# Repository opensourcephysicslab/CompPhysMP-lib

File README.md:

# Computational Physics MicroPython libraries

## Introduction
This repo contains MicroPython code developed to support computational physics in a laboratory setting, mainly reading data from sensors and displaying results.

## Concept of unified and simplified drivers/modules

In order to make computational physics laboratory activities an enjoyable experience for students and instructors, the developer(s) have made simplified drivers that focus on the key features of sensors with a unified interface among sensors of the same type.

For instance, LIS3HD and ADX345 are 3-axis accelerometers made by different companies with different accuracy and features that make them not exactly interchangeable. But by the magic of unification, regardless which accelerometer you choose to use, a call to accelerometer.read_mss() will always return a tuple of accelerations (actually, force over a fixed mass) in m/s/s unit such as (0.15,-0.23,9.72).

In pursuing for this unified interface for a beginner's sake, the differences among sensors of the same type are NOT addressed, such as some accelerometers have up to 400Hz data rate and others have extended range such as +-16g, yet some can detect knock, double click, issue interrupts under certain conditions (such as free falling). This is definitely an oversimplification of what each sensor can do.

The outcome is hopefully a quick way to utilizing the sensors with minimal efforts.

Also, those who are curious about how these sensors work will find the oversimplified drivers/modules code much easier to understand compared with a more "full feature" driver. In each case, the user is strongly encouraged to consult the sensor's specification sheet. 

To address the omission of some sensor features, other github repos that have "full feature" drivers/modules are included as submodules. These have been tested to work on at least one MicroPython platform, i.e. RP2040, if not more.

## A warning:

Compared with the more unified writing styles of the drivers/modules, the included submodules were all written by different developers, each having their own styles and conventions. It is like watching YouTube videos of physics lectures from different professors. Each one has their own symbols and styles so it could be disorienting for beginners. Reading the unified drivers/modules code before a "full feature" module is highly recommended. For support on any submodules, please contact the developers of those submodules.

## Conventions:

Any files or folders named Driver_[git_handle]_[sensor_model] is a unified and simplified driver/module. Example: Driver_LiuDr_LIS3DH.py

Any unified and simplified driver/module MUST define an embedded example with 
`if __name__=='_main__'` conditional and assume the sensor is connected to an Adafruit KB2040 via the STEMMA-QT connector, with no other dependency. So if executed directly will provide a basic printout in console such as printing ax,ay,az for an accelerometer or temperature and pressure for a barometer.

## Installation:

The Adafruit KB2040 is recommended. It is small, inexpensive, and has a large file storage, albeit not a RAM size. It also has a STEMMA-QT connector that can help students and instructors quickly set up an experiment without breadboard experiece [KB2040](https://www.adafruit.com/product/5302)

You need to solder headers to your KB2040. The [primary guide](https://learn.adafruit.com/adafruit-kb2040/overview) has tutorial on how to.

The Thonny IDE is highly recommended for editing your code and interacting with your board and sensors. [Thonny](https://thonny.org/)

You can install MicroPython firmware to some of the dev board via Thonny. For KB2040, download the firmware for Adafruit Feather RP2040 (same firmware as KB2040) [here](https://micropython.org/download/ADAFRUIT_FEATHER_RP2040/). Hold the boot button, plug in to USB, wait for a moment and release the boot button. The board enumerates a flash drive. Drag+drop the firmware into the flash drive. The firmware will cause the flash drive to disappear. After about 30 seconds, you can press reset and go to Thonny to connect to it.

Cloning this repo is highly recommended but for simplicity you can just download the repo in a .zip file. Copy lib folder to the root folder of your MicroPython board. Be mindful how many external submodules you are copying. The recommendation is to not copy anything in lib that doesn't start with Driver_[git_handle].py unless the example code requires certain files.

Example code is in the top-level folder and can be copied to the root folder of your MicroPython board. Example: copy LIS3DH_SH1117_display.py to your board. Open the example and read the comments at the top to see what hardware you need and what library you need to copy to what destination.

All example code are written for Adafruit KB2040 board. If you are using a different board, open the code and make necessary changes to the 'i2c=I2C(...)' line to match your board. Then run this code in Thonny.

## Submodules not included

Some git projects that include full-feature drivers/modules are not included as submodules in this repo because of various reasons. One of them would be the repo contains more than just a MicroPython sensor driver/module but also other things not related to our efforts, such as custom firmware images for specific boards, circuit board designs etc. When such inclusion becomes too confusing to include, the repo's link will be included below with some explanation on where the driver/module is.

[tinypico](https://github.com/tinypico/tinypico-micropython) includes an LIS3DH MicroPython driver that is tested to work, with extended features.

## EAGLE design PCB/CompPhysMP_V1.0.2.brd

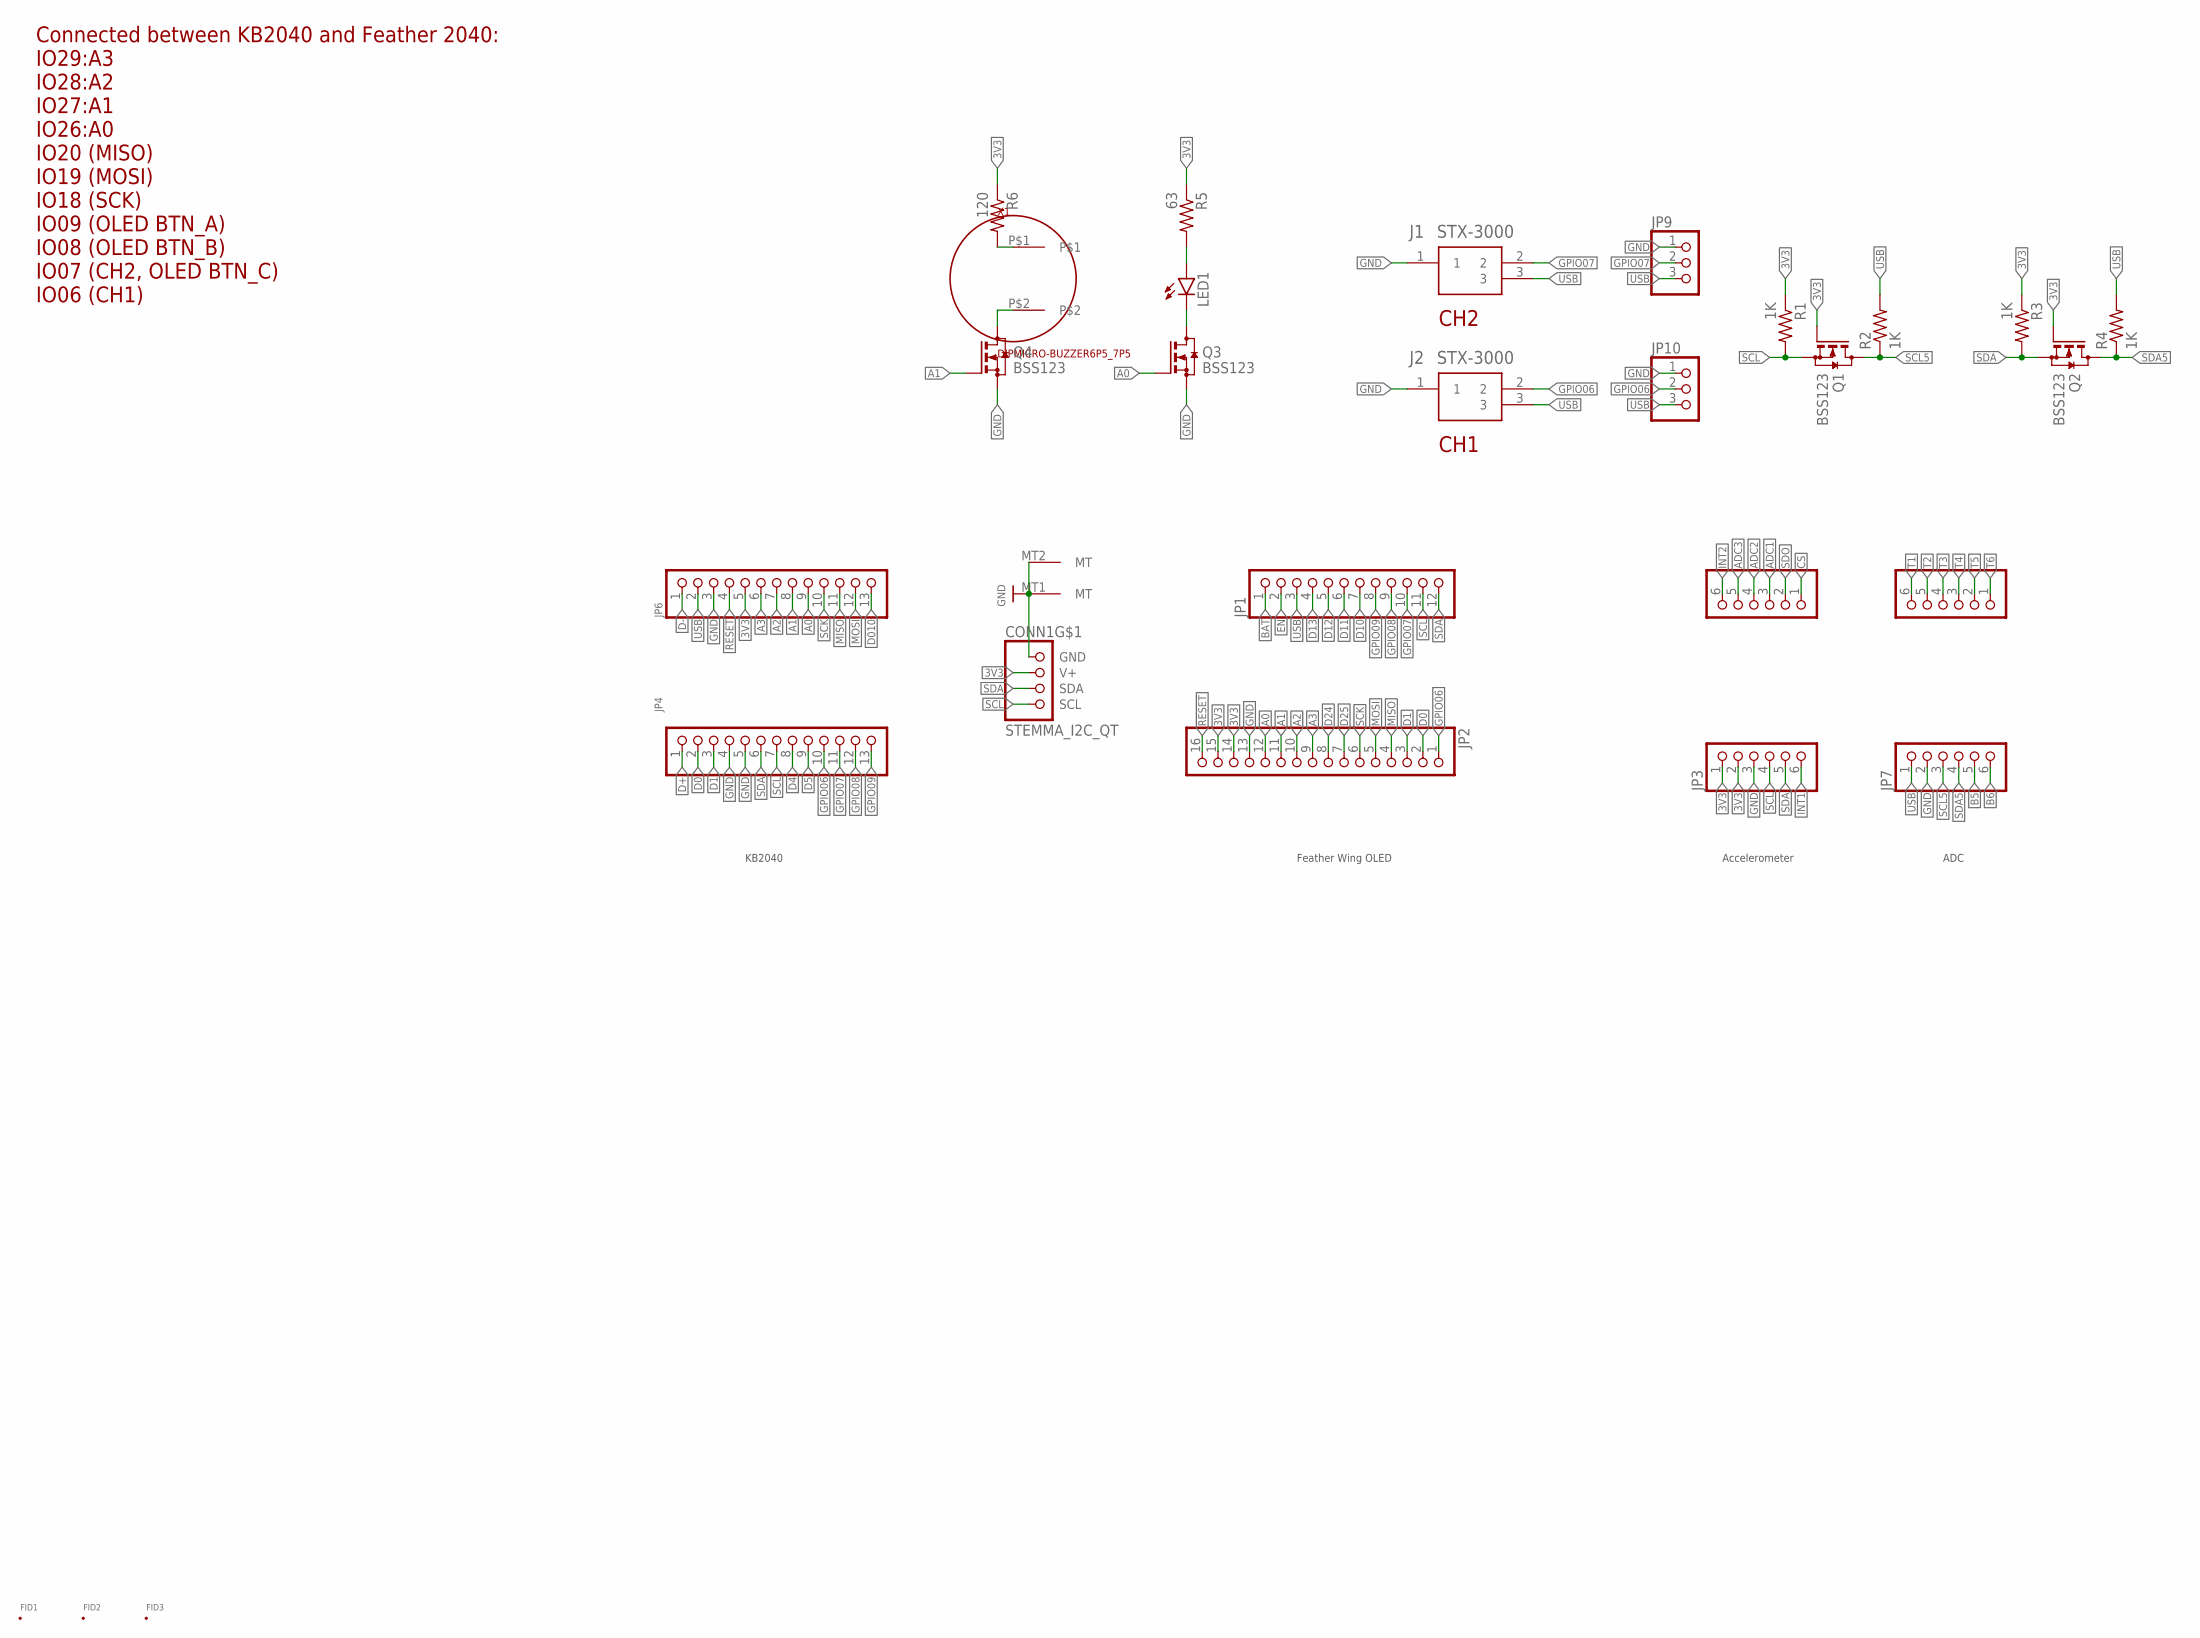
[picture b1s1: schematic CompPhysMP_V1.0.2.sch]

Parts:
CONN1: STEMMA_I2C_QT; JST_SH4
FID1, FID2, FID3: FID_50MIL; FID_050
J1, J2: STX-3000; STX3000
JP1: PINHD-1X12; 1X12
JP2: PINHD-1X16; 1X16
JP3, JP5, JP7, JP8: HEADER-1X670MIL; 1X06_ROUND_70
JP4, JP6: PINHD-1X13; 1X13
JP9, JP10: PINHD-1X3SMALL-PADS; 1X03-BIG
LED1: LED5MM
Q1, Q2, Q3, Q4: BSS123; SOT23
R1, R2, R3, R4: 1K; R0805
R5: 63; R0805
R6: 120; R0805
X1: DIPMICRO-BUZZER6P5_7P5; BUZZER-6P5-7P5

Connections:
3V3: CONN1.2 (V+), JP2.14, JP2.15, JP3.1, JP3.2, JP6.5, Q1.1 (G), Q2.1 (G), R1.1, R3.1, R5.1, R6.1
!RESET: JP2.16, JP6.4
A0: JP2.12, JP6.9, Q3.1 (G)
A1: JP2.11, JP6.8, Q4.1 (G)
A2: JP2.10, JP6.7
A3: JP2.9, JP6.6
ADC1: JP5.3
ADC2: JP5.4
ADC3: JP5.5
B5: JP7.5
B6: JP7.6
BAT: JP1.1
CS: JP5.1
D0: JP2.2, JP4.2
D1: JP2.3, JP4.3
D4: JP4.8
D5: JP4.9
D10: JP1.7
D010: JP6.13
D11: JP1.6
D12: JP1.5
D13: JP1.4
D24: JP2.8
D25: JP2.7
D+: JP4.1
D-: JP6.1
EN: JP1.2
GND: CONN1.1 (GND), CONN1.MT1 (MT), CONN1.MT2 (MT), J1.1, J2.1, JP2.13, JP3.3, JP4.4, JP4.5, JP6.3, JP7.2, JP9.1, JP10.1, Q3.2 (S), Q4.2 (S)
GPIO06: J2.2, JP2.1, JP4.10, JP10.2
GPIO07: J1.2, JP1.10, JP4.11, JP9.2
GPIO08: JP1.9, JP4.12
GPIO09: JP1.8, JP4.13
INT1: JP3.6
INT2: JP5.6
MISO: JP2.4, JP6.11
MOSI: JP2.5, JP6.12
unnamed: LED1.A, R5.2
unnamed: R6.2, X1.P$1
unnamed: LED1.K (C), Q3.3 (D)
unnamed: Q4.3 (D), X1.P$2
SCK: JP2.6, JP6.10
SCL: CONN1.4 (SCL), JP1.11, JP3.4, JP4.7, Q1.2 (S), R1.2
SCL5: JP7.3, Q1.3 (D), R2.1
SDA: CONN1.3 (SDA), JP1.12, JP3.5, JP4.6, Q2.2 (S), R3.2
SDA5: JP7.4, Q2.3 (D), R4.1
SDO: JP5.2
T1: JP8.6
T2: JP8.5
T3: JP8.4
T4: JP8.3
T5: JP8.2
T6: JP8.1
USB: J1.3, J2.3, JP1.3, JP6.2, JP7.1, JP9.3, JP10.3, R2.2, R4.2

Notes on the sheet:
Accelerometer
ADC
Feather Wing OLED
KB2040
Connected between KB2040 and Feather 2040: IO29:A3 IO28:A2 IO27:A1 IO26:A0 IO20 (MISO) IO19 (MOSI) IO18 (SCK) IO09 (OLED BTN_A) IO08 (OLED BTN_B) IO07 (CH2, OLED BTN_C) IO06 (CH1)
CH1
CH2

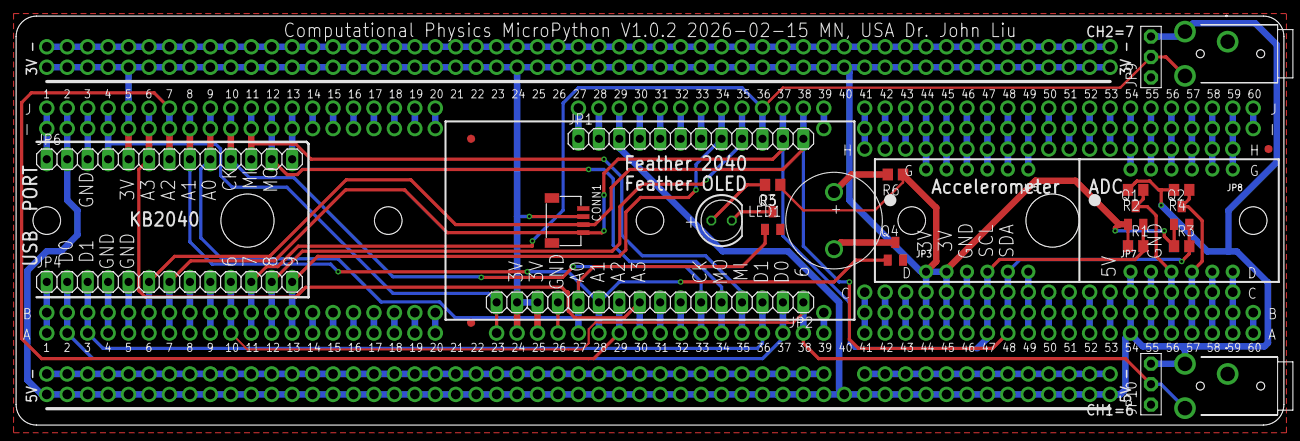
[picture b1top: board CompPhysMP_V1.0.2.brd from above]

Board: 2 copper layers, 157.5 x 50.8 mm, 28 parts (0 on the bottom side), 25 nets.

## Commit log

2024-10-18 Initial commit
    Adding 3 LiuDr drivers and several micropython libraries as submodules.
2024-10-18 Create LIS3DH_SH11107_display.py
    Example to show acceleration components and x-tilt angle on console and display x-tilt angle on OLED.
2024-10-18 Moved example code to top-level folder
2024-10-18 Update README.md
    Added detailed instructions on how to install MicroPython, where to download firmware and Thonny.
2024-10-25 Update LIS3DH_SH11107_display.py
    Made the free fall detection display persist for 2 seconds for people to see.
2024-10-26 Added spec sheets
2024-10-27 Update LIS3DH_SH11107_display.py
    Using atan2 now and cleaned up print() statement
2024-11-02 Added dev board pinout diagrams and an rp2040 analog print program
2024-11-05 Update README.md
    Minor edits
2024-11-13 Updated ADXL345 and LIS3DH modules to accept useDefaultAddr=True/False for default or alternate address
2025-02-10 Added a two-rectangle rotation demo with LIS3DH and SH1107 and updated original code
    The two-rectangle rotation demo is an application of 2D rotation matrix to rotate the corners of the rectangles.
    One can also approximate sine and cosine with ax and ay with a zooming effect.
    Fixed naming error SH11107 to SH1107
2025-02-11 Added polygon rotation code
    Also added description of how to create the polygon
2025-02-12 Update LIS3DH_SH1107_display_polygon.py
    Added an SCSU Husky outline, center, and scale
    Added more comments at the top of the script
2025-03-26 Create Photogate_detection.py
    For projectile motion lab
2025-04-03 Updated code
    Making code more readable
2025-04-04 Updated projectile lab scripts
    Now 3 scripts exist:
    1: measure launch speed
    2: measure launch speed and predicts distance with a given angle
    3: predicts distance based on accelerometer-measured angle and past launch speed. Immediately after launch, predict new distance based on new launch speed.
    Roughly speaking, 3 includes all of 2 which includes all of 1. So start with 1 and progress to 2. If time permits, do 3.
2025-04-08 Updated photogate pins to 28 and 29
    Reserved pins 0 and 1 for UART with other devices.
2025-04-09 Create Rotation_lab1.py
    Added a draft script to sense average rotational speed of pulley or other rotating platforms.
2025-04-20 Added free fall and tone generator code
    Free fall with blinking LED
    Tone generator as an indicator
2025-04-22 Swapped while loop and interrupt so while loop is the default in projectile
    The angle is corrected for the orientation of the CompPhysMP board.
    Also swapped methods 1 and 2 so the default is 1: while loop
    Created a simple projectile lab routine with minimal description and comments
2025-04-22 Create Print_photogate_event_ticks.py
    This script prints out any HIGH->LOW event's time tick from either gate.
    Ctrl-C to stop it.
    You can use this script to capture rotation stage angles if there's any structure on the stage that can block light, like the 4 spokes on our stage. You can also use this as a primitive way read phot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
2025-04-22 Update Freefall_lab.py
    Updated frequency to 100Hz
2025-04-23 Updated photogate event ticks program
    Added a version that buffers the print until the trial is over.
2025-04-28 Adding PCB design and production files
    Ignore .DS_Store from mac
    First commit of PCB design and production files
2025-04-29 Create test_ads1115.py
    Added code to test ADS1115 breakout boards.
2025-05-02 Updated PCB V1.0.1
    Updated the resistance values from 1000 to 1K
    Updated speaker resistor to 120
    Updated LED resistor to 63
    Updated fiducial names from FDn FDIn
    Added .mnt file.
2025-05-23 Update LIS3DH_SH1107_display_polygon.py
    Added I2C settings for CompPhysMP and RP2040 and make it default.
    Select either the setting for KB2040 or CompPhysMP/RP2040.
2025-06-08 Create CompPhysMP_V1.0.1.csv
    For pick-n-place machine
2025-07-02 Inlined some comments and corrected spelling errors
2025-07-04 Update Projectile_lab1.py
    Removed method 2
2025-10-27 Added a couple more polygons
    Added new polygons in polygons.py
    Also reordered when to clear display
2025-10-28 Create polygon_rotation.py
    This script demonstrates rotation without using any electronics featured in the videos. It can be used to explain the basics of the math involved.
2026-01-08 Added Accelerometer_to_console.py and ADXL343.pdf
    Use this for accelerometer on a ramp lab
2026-01-08 Corrected error in ADXL345 driver
    Also confirmed that it works for ADXL343.
    Updated Accelerometer_to_console.py
2026-01-21 Create Freefall_lab_short.py
    This flashes the LED on the board using minimal lines of code.
2026-01-27 Added LED fader, updated polygon script
    LED fader helps students understand PWM and you can easily observe it on a scope.
    Updated polygon script has optional lines to use ADXL343 or ADXL345 instead of LIS3DH.
2026-02-16 Updated PCB with a few changes
    PCB 1.0.2
    Changed CH1 and CH2 pins. Connected more pins between KB2040 and Feather 2040. Added more markings on silk screen.
    Didn't change any SMD components so pnp file is the same as 1.0.1.
2026-02-16 Updated code to support PCB V1.0.2 CH1 and CH2
    Also added Projectile_lab0.py as a simple script.
2026-02-17 Create V1_0_1_to_V1_0_2.txt
    Follow this to modify V1.0.1 board into V1.0.2 board.
2026-02-26 Added Newton's Law lab code
    Two PASCO photogates and glider with an attachment.
2026-03-05 Improved projectile launcher prediction routine
    Added a prediction routine with calibrated angles for more accuracy.
    Added a servo motor test routine.
    Added laser pointer routine in projectile4.
    Added some Kikad file.
2026-03-10 Added DotStar library and projectile launcher with DotStar prediction LED strip
2026-03-10 Update Projectile_lab5.py
    Added color definitions and updated speed.
2026-03-12 Corrected error in formula

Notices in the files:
parts and their libraries:
microbuilder: This work is placed in the public domain, and may be freely used for commercial and non-commercial work with the following conditions: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
